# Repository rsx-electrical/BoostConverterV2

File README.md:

# BoostConverterV2 (Ignore 'V3' on file names)
Alternate Boost Converter design with a lateral switching power loop for improved thermal management. Voltages up to 80V for voltages above the battery rail, with 19V case possible of continuous 200W power production.

BoostConverterV1 is in the BoostConverter repo. This V2 is meant to contrast the capabilities of V1 with varying High-side/Low-side MOSFET arrangement, observing any changes in performance with differing switching power loops, potentially lowering regulator EMI signature on the board(s).

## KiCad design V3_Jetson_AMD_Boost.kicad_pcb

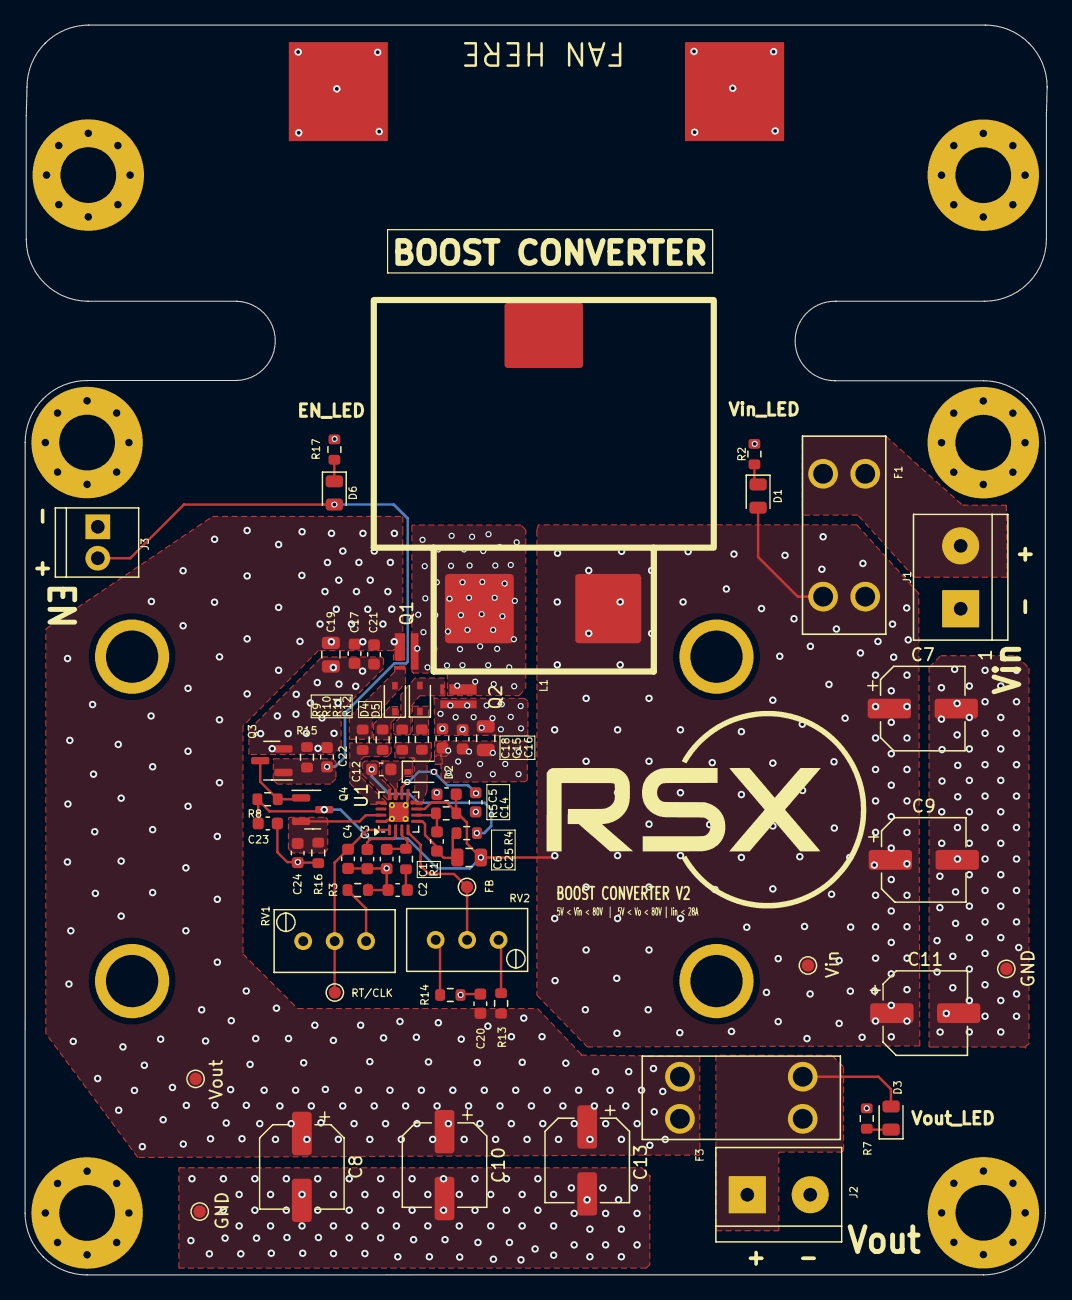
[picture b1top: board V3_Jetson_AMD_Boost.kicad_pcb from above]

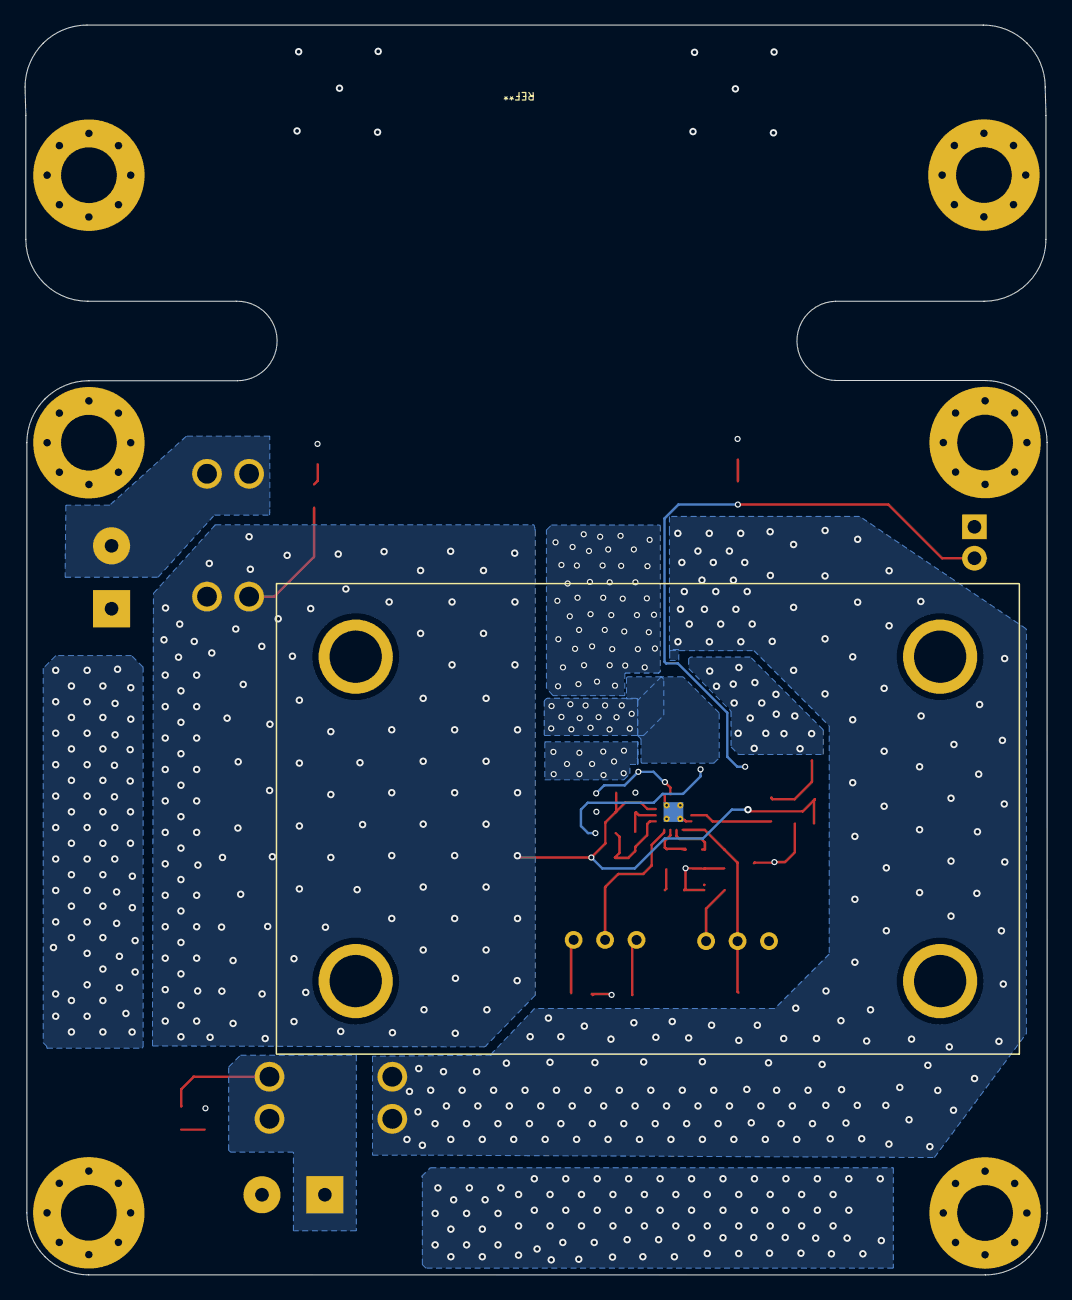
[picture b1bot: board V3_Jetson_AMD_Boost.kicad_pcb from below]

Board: 4 copper layers, 82.5 x 100.9 mm, 74 parts (2 on the bottom side), 29 nets.

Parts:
C1: 1.5nf; C_0603_1608Metric
C2: 33nf; C_0603_1608Metric
C3, C4, C5, C12, C15, C17, C18, C20, C21, C22, C23, C24: 0.1uf; C_0603_1608Metric
C6: 0.1 uf; C_0603_1608Metric
C7, C8, C9, C10, C11, C13: 100uf; CP_Elec_6.3x7.7
C14: 4.7uf; C_0603_1608Metric
C16, C19, C25: 1uf; C_0805_2012Metric
D1, D3, D6: LED_G; LED_0805_2012Metric
D2, D4, D5: D_Schottky; D_SOD-323
F1, F3: Fuse_Holder_Auto; FUSE_3568-10
F2: 40mm_by_20mm_Fan_Vertical; 40mmFan
FB: TestPoint; TestPoint_Pad_D1.0mm
GND: TestPoint; TestPoint_Pad_D1.0mm
GND#2: TestPoint; TestPoint_Pad_D1.0mm
H2, H2#2, H2#3, H2#4, H2#5, H2#6: M2 PLATED; MountingHole_4.5mm_Pad_Via
HW1: Board_Mount_Heat_Sink_Screw_2.5C/W; ATS-1139-C1-R0
J1, J2: Screw_Terminal_01x02; Molex_0398800302
J3: Screw_Terminal_01x02; Wurth_691210910002
L1: 15uH; PQ2617BHA-XXXK
Q1, Q2: GAN7R0-150LBEZ
Q3: 2N7002K; SOT-23
Q4: BSS83P; SOT-23
R1: 15k; R_0603_1608Metric
R2, R7, R17: 4K7; R_0603_1608Metric
R3, R13: 150k; R_0603_1608Metric
R4, R5: 750; R_0603_1608Metric
R8, R14, R15, R16: 10k; R_0603_1608Metric
R9, R10, R11, R12: 1; R_0603_1608Metric
RT/CLK: TestPoint; TestPoint_Pad_D1.0mm
RV1, RV2: 100k; Potentiometer_Bourns_3296W_Vertical_DL
U1: TPS43060RTE; WQFN-16-1EP_3x3mm_P0.5mm_EP1.6x1.6mm_ThermalVias
Vin: TestPoint; TestPoint_Pad_D1.0mm
Vout: TestPoint; TestPoint_Pad_D1.0mm

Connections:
/BOOT: C12.1, D2.1 (K), U1.11 (BOOT)
/COMP: C1.1, R1.1, U1.3 (COMP)
/HDRV: D4.2 (A), Q1.1, R9.2
/HDRV_CTRL: R9.1, R10.1, U1.13 (HDRV)
/LDRV: D5.2 (A), Q2.1, R11.2
/LDRV_CTRL: R11.1, R12.1, U1.8 (LDRV)
/RT/CLK: C4.1, RT/CLK.1, RV1.2, U1.1 (RT/CLK)
/SS: C3.1, U1.2 (SS)
/Vcc: C14.1, D2.2 (A), U1.10 (VCC)
Bat: F1.1, J1.2
ENABLE: C22.2, D6.2 (A), J3.2, Q3.1 (G), R15.1
EN_CTRL: C24.1, Q4.2 (S), R16.1, U1.15 (EN)
FB: FB.1, RV2.2, U1.4 (FB)
GND: C1.2, C2.2, C3.2, C4.2, C5.2, C7.2, C8.2, C9.2, C10.2, C11.2, C13.2, C14.2, C15.1, C16.1, C17.2, C18.1, C19.2, C20.2, C21.2, C22.1, C23.2, C24.2, F2.1, GND.1, GND#2.1, H2.1, H2#2.1, H2#3.1, H2#4.1, H2#5.1, H2#6.1, HW1.1, HW1.2, HW1.3, HW1.4, J1.1, J2.2, J3.1, Q2.2, Q3.2 (S), R2.2, R3.2, R7.2, R14.1, R15.2, R16.2, R17.2, U1.9 (PGND), U1.16 (AGND), U1.17 (AGND)
ISNS+: C6.1, R5.1, U1.6 (ISNS+)
ISNS-: C6.2, C25.1, R4.1, U1.5 (ISNS–)
unnamed: C2.1, R1.2
unnamed: D1.1 (K), R2.1
unnamed: D3.1 (K), R7.1
unnamed: D4.1 (K), R10.2
unnamed: D5.1 (K), R12.2
unnamed: D6.1 (K), R17.1
unnamed: Q3.3 (D), Q4.1 (G), R8.1
unnamed: R3.1, RV1.3
unnamed: R13.2, RV2.1
unnamed: R14.2, RV2.3
SW: C12.2, L1.1, Q1.2, Q2.3, R4.2, U1.12 (SW)
Vin: C5.1, C7.1, C9.1, C11.1, C23.1, C25.2, D1.2 (A), F1.2, L1.2, Q4.3 (D), R5.2, R8.2, U1.7 (VIN), Vin.1
Vout: C8.1, C10.1, C13.1, C15.2, C16.2, C17.1, C18.2, C19.1, C20.1, C21.1, D3.2 (A), F3.1, F3.2, J2.1, Q1.3, R13.1, Vout.1

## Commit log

2025-03-15 README.md
2025-08-15 generated step file

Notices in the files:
parts and their libraries:
Copyright 2016 Accelerated Designs. All rights reserved.
